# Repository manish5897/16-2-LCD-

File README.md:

# 16-2-LCD-
16*2 LCD, schematic and layout in eagle cadsoft

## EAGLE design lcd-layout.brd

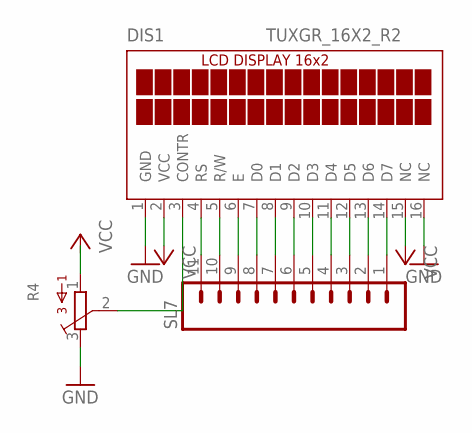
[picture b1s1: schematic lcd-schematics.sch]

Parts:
DIS1: TUXGR_16X2_R2
R4: 3362P
SL7: M11; 11P

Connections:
GND: DIS1.1 (GND), DIS1.16 (NC), R4.3
unnamed: DIS1.14 (D7), SL7.1
unnamed: DIS1.13 (D6), SL7.2
unnamed: DIS1.12 (D5), SL7.3
unnamed: DIS1.11 (D4), SL7.4
unnamed: DIS1.10 (D3), SL7.5
unnamed: DIS1.9 (D2), SL7.6
unnamed: DIS1.8 (D1), SL7.7
unnamed: DIS1.7 (D0), SL7.8
unnamed: DIS1.6 (E), SL7.9
unnamed: DIS1.5 (R/W), SL7.10
unnamed: DIS1.4 (RS), SL7.11
unnamed: DIS1.3 (CONTR), R4.2
VCC: DIS1.2 (VCC), DIS1.15 (NC)

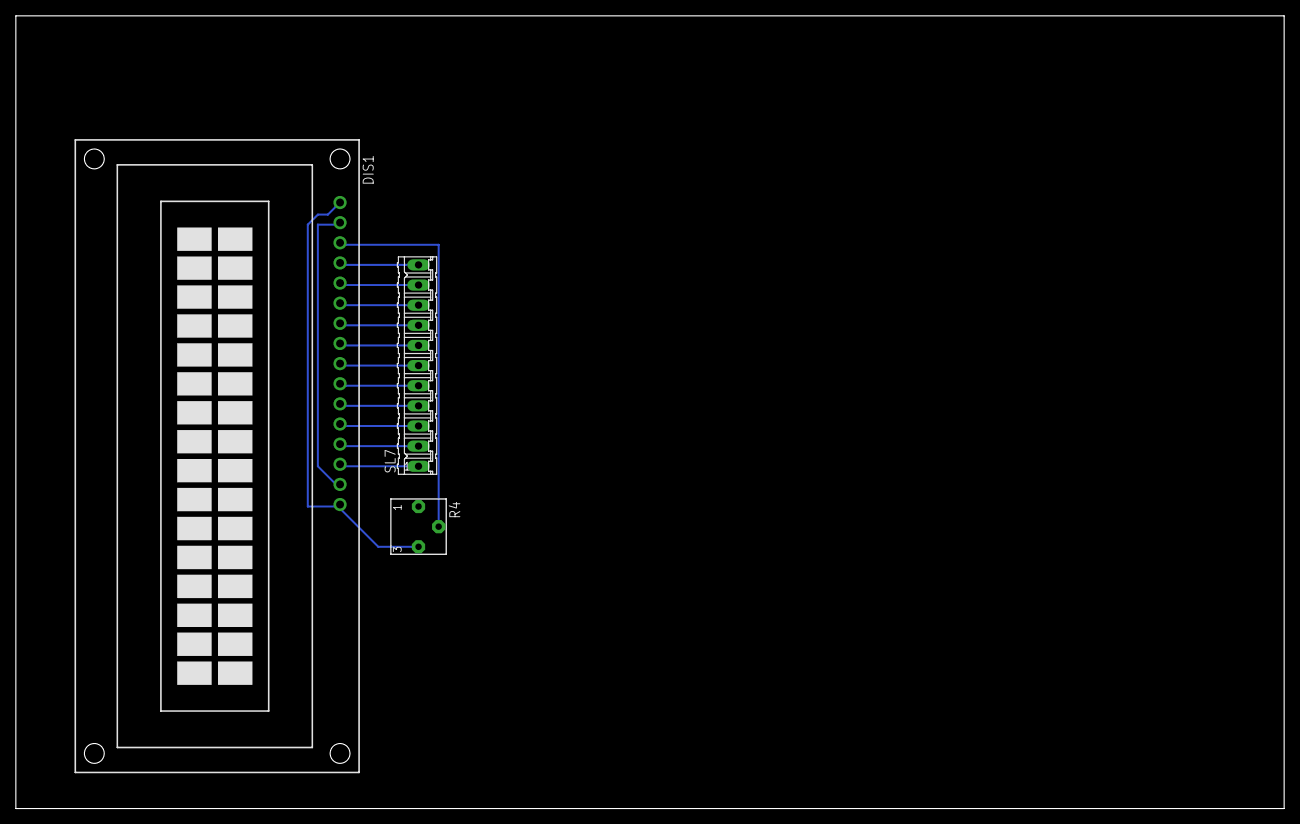
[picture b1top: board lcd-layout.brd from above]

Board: 2 copper layers, 160.0 x 100.0 mm, 3 parts (0 on the bottom side), 14 nets.

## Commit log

2018-08-13 16*2 LCD schematic and board file in eagle
